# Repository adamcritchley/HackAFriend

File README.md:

# Hack-A-Friend Handheld Gaming Console

### Hone your hacking skills with the **Hack-A-Friend** gaming handheld!  
Delve into epic **CTF attack and defend** style games with your friends. Challenge opponents by **attacking their devices** while defending your own. The winner unleashes a **devastating payload** to dominate their opponent’s game.

---

## 🔥 Features

- **CTF-style gameplay** – Attack and defend devices in real-time battles.
- **Custom payloads** – Winners can craft unique in-game exploits.
- **Open-source** – Clone our upcoming [GitHub repository](#) and create your own games and payloads.
- **Interactive LEDs** – Visual cues for game status and exploit notifications.
- **Bootloader customization** – Recover or modify firmware when needed.

---

## 🔧 Hardware Specifications

- **Power System**:
  - Lithium-ion battery management chip.
  - 500mA LDO for regulated power.
  - Test points for monitoring:
    - `VCC` (battery power source).
    - `3V3` (regulated output from LDO).

- **LED Indicators**:
  - **System notifications**:
    - `PWR` (Power Health LED).
    - `CHG` (Battery Charging LED).
  - **Game Status**:
    - **NeoPixel**:
      - Off – Game idle.
      - Green – Game active.
      - Red – Device under exploitation.
    - **User-Controlled LEDs**:
      - Two standard LEDs for custom exploit visualizations.

- **Debugging & Recovery**:
  - **Test points** for SDA & SCL (I2C debugging with digital signal analyzer).
  - **Bootloader Recovery**:
    - Uses **10-pin ARM TagConnect footprint** (`TC2050-IDC-NL` cable).
    - Compatible with **SWD** and **JTAG** devices like `nRF52840 DK`.
    - Recovery via `nrf-utils` and official bootloader image.
    - **Segger J-Link compatibility

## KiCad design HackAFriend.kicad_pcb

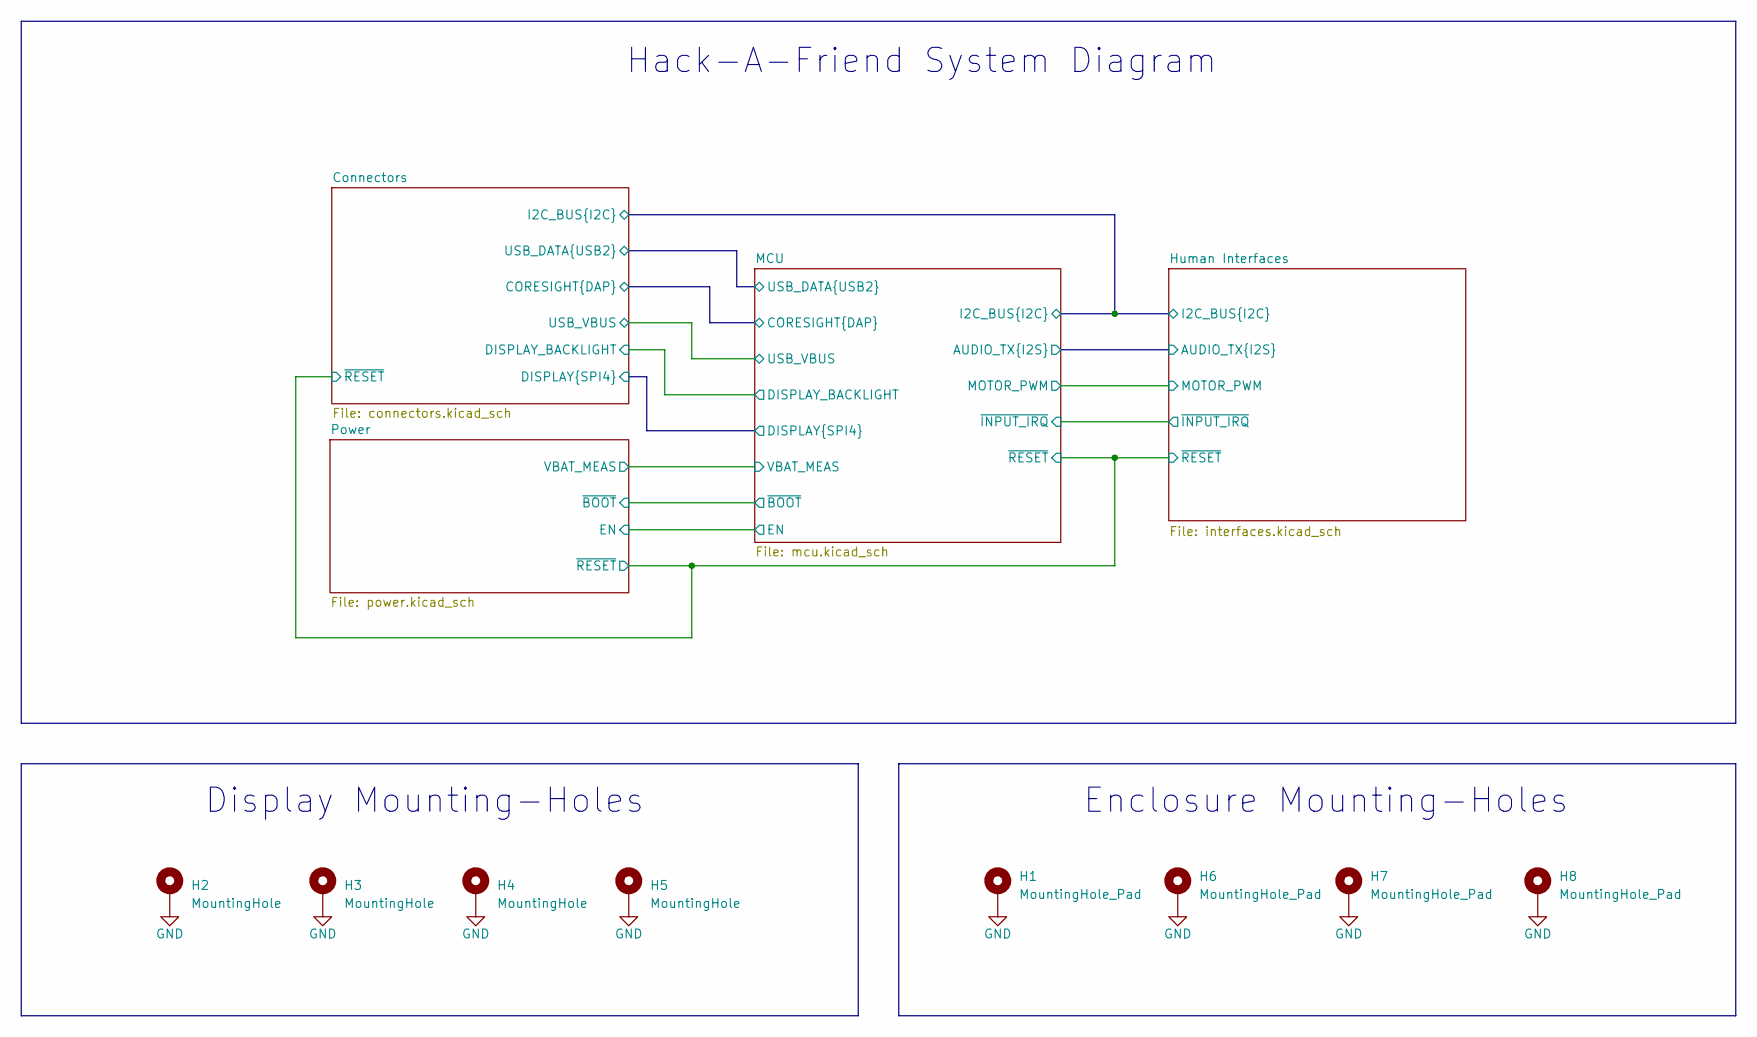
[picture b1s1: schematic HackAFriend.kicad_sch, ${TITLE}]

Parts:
H1, H6, H7, H8: MountingHole_Pad; MountingHole_2.7mm_M2.5_DIN965_Pad
H2, H3, H4, H5: MountingHole; MountingHole_2.5mm_Pad

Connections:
GND: H1.1, H2.1, H3.1, H4.1, H5.1, H6.1, H7.1, H8.1; also elsewhere on the board

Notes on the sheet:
Display Mounting-Holes
Hack-A-Friend System Diagram
Enclosure Mounting-Holes

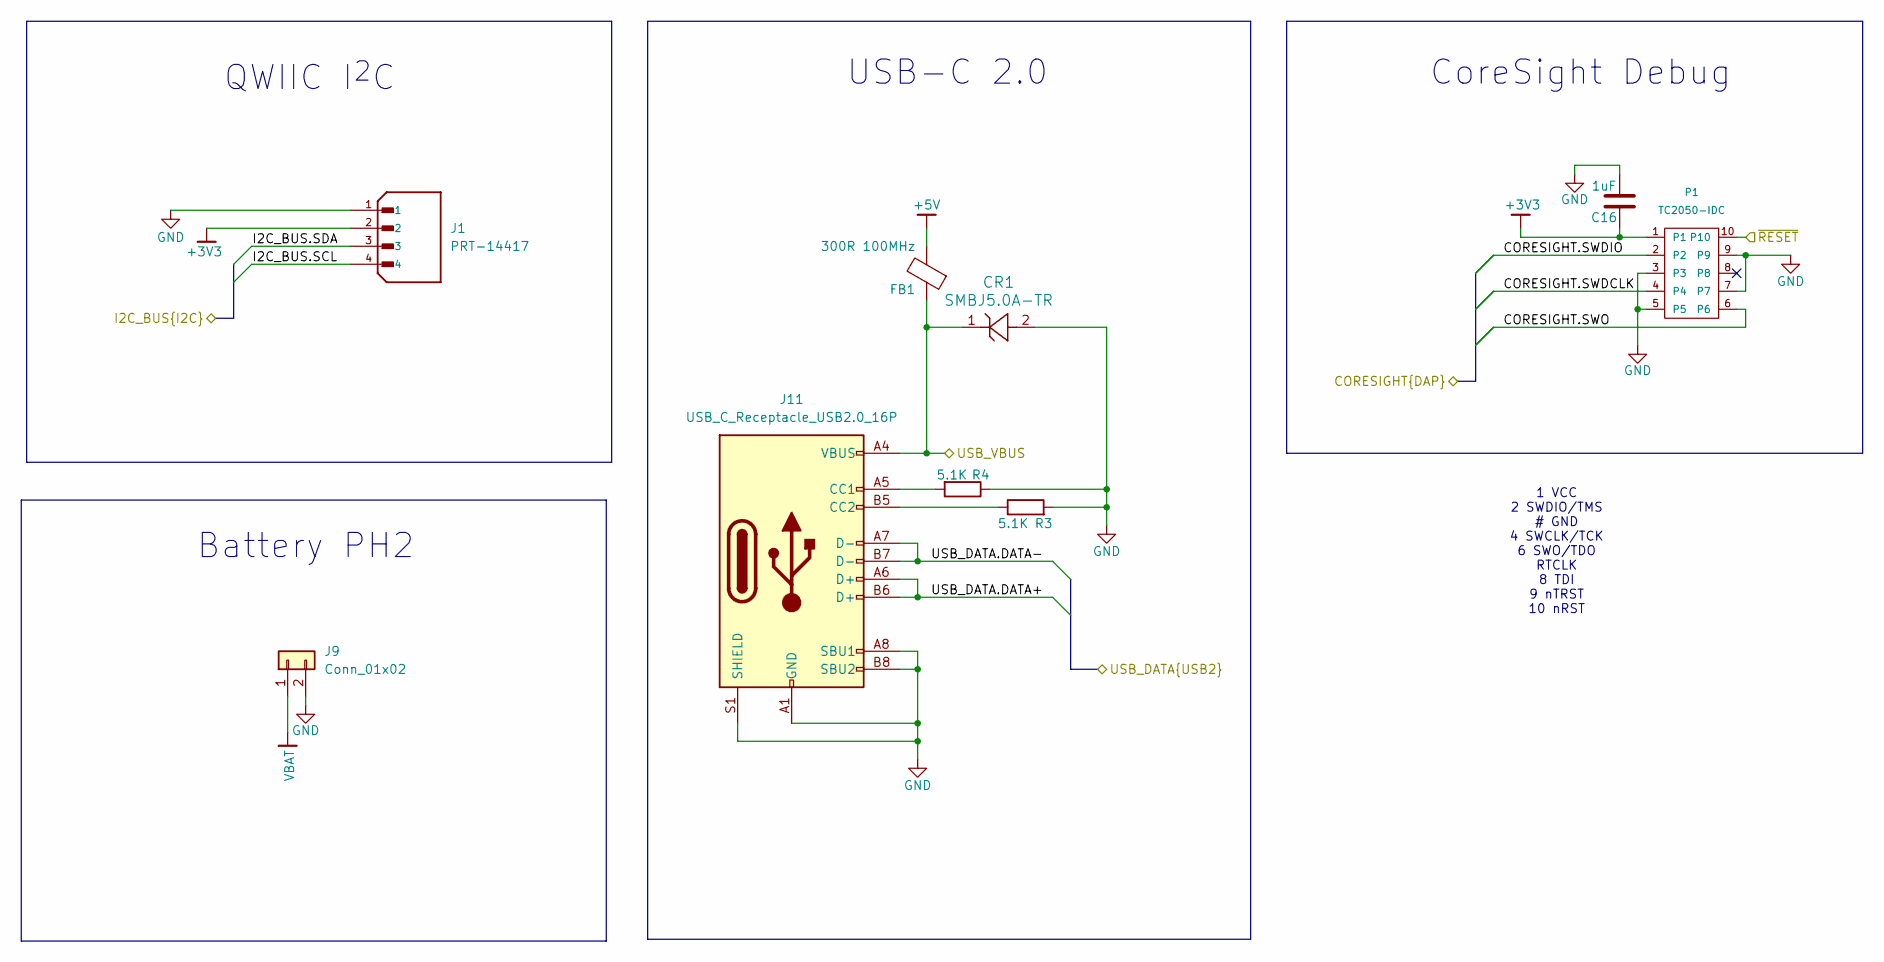
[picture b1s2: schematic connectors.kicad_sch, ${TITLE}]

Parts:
C16: 1uF; C_0402_1005Metric
CR1: SMBJ5.0A-TR; SMB_STM
FB1: 300R 100MHz; L_0805_2012Metric
J1: PRT-14417; SPARKFUN_PRT-14417; PARTREV NA
J9: Conn_01x02; JST_PH_S2B-PH-K_1x02_P2.00mm_Horizontal
J11: USB_C_Receptacle_USB2.0_16P; USB_C_Receptacle_GCT_USB4105-xx-A_16P_TopMnt_Horizontal
P1: TC2050-IDC; Tag-Connect_TC2050-IDC-FP_2x05_P1.27mm_Vertical
R3, R4: 5.1K; R_0402_1005Metric

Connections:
+3V3: C16.1, J1.2, P1.1; also elsewhere on the board
+5V: FB1.2; also elsewhere on the board
/Connectors/CORESIGHT.SWDCLK: P1.4; also elsewhere on the board
/Connectors/CORESIGHT.SWDIO: P1.2; also elsewhere on the board
/Connectors/CORESIGHT.SWO: P1.6; also elsewhere on the board
/Connectors/I2C_BUS.SCL: J1.4; also elsewhere on the board
/Connectors/I2C_BUS.SDA: J1.3; also elsewhere on the board
/Connectors/USB_DATA.DATA+: J11.A6 (D+), J11.B6 (D+); also elsewhere on the board
/Connectors/USB_DATA.DATA-: J11.A7 (D-), J11.B7 (D-); also elsewhere on the board
/Connectors/USB_VBUS: CR1.1, FB1.1, J11.A4 (VBUS), J11.A9 (VBUS), J11.B4 (VBUS), J11.B9 (VBUS); also elsewhere on the board
/Connectors/~RESET: P1.10; also elsewhere on the board
GND: C16.2, CR1.2, J1.1, J9.2, J11.A1 (GND), J11.A8 (SBU1), J11.A12 (GND), J11.B1 (GND), J11.B8 (SBU2), J11.B12 (GND), J11.S1 (SHIELD), P1.3, P1.5, P1.7, P1.9, R3.2, R4.1; also elsewhere on the board
unnamed: J11.A5 (CC1), R4.2
unnamed: J11.B5 (CC2), R3.1
VBAT: J9.1; also elsewhere on the board

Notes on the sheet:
USB-C 2.0
Battery PH2
QWIIC I^{2}C
1 VCC 2 SWDIO/TMS # GND 4 SWCLK/TCK 6 SWO/TDO RTCLK 8 TDI 9 nTRST 10 nRST
CoreSight Debug

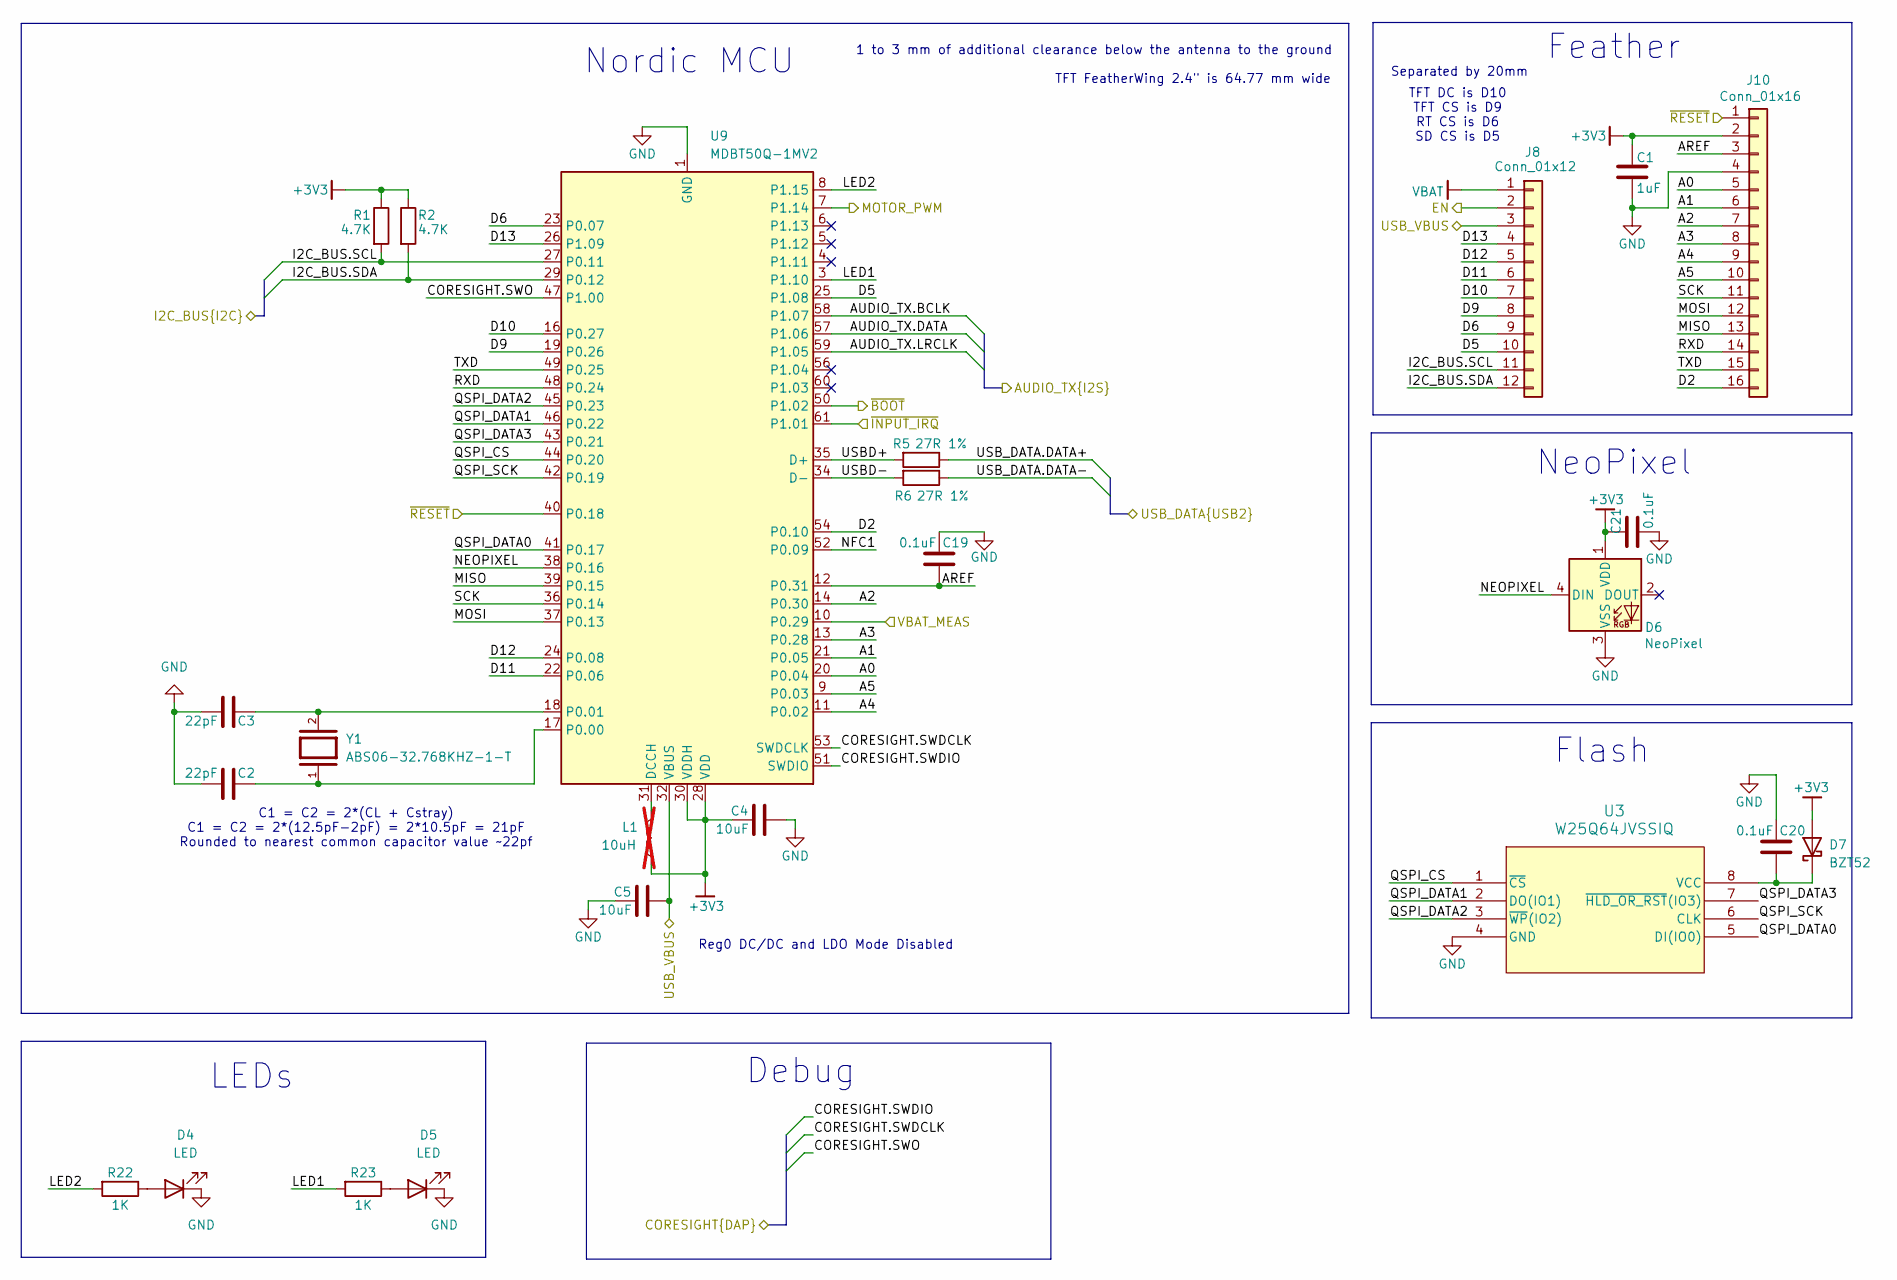
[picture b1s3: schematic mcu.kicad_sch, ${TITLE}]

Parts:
C1: 1uF; C_0402_1005Metric
C2, C3: 22pF; C_0603_1608Metric
C4, C5: 10uF; C_0603_1608Metric
C19, C20, C21: 0.1uF; C_0402_1005Metric
D4, D5: LED; LED_0603_1608Metric
D6: NeoPixel; LED_WS2812B_PLCC4_5.0x5.0mm_P3.2mm
D7: BZT52; D_0402_1005Metric
J8: Conn_01x12; PinHeader_1x12_P2.54mm_Vertical_SMD_Pin1Left
J10: Conn_01x16; PinHeader_1x16_P2.54mm_Vertical_SMD_Pin1Left
L1: 10uH; L_0603_1608Metric; not fitted
R1, R2: 4.7K; R_0603_1608Metric
R5, R6: 27R 1%; R_0402_1005Metric
R22, R23: 1K; R_0603_1608Metric
U3: W25Q64JVSSIQ; SOIC-8_5P28X5P28_WIN
U9: MDBT50Q-1MV2; Raytac_MDBT50Q
Y1: ABS06-32.768KHZ-1-T; XTAL_ABS06-32.768KHZ-1-T; PARTREV 4/25/2022

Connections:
+3V3: C1.1, C4.2, C21.2, D6.1 (VDD), D7.2 (A), J10.2, L1.1, R1.1, R2.1, U9.28 (VDD), U9.30 (VDDH); also elsewhere on the board
/Connectors/CORESIGHT.SWDCLK: U9.53 (SWDCLK); also elsewhere on the board
/Connectors/CORESIGHT.SWDIO: U9.51 (SWDIO); also elsewhere on the board
/Connectors/CORESIGHT.SWO: U9.47 (P1.00); also elsewhere on the board
/Connectors/I2C_BUS.SCL: J8.11, R1.2, U9.27 (P0.11); also elsewhere on the board
/Connectors/I2C_BUS.SDA: J8.12, R2.2, U9.29 (P0.12); also elsewhere on the board
/Connectors/USB_DATA.DATA+: R5.1; also elsewhere on the board
/Connectors/USB_DATA.DATA-: R6.1; also elsewhere on the board
/Connectors/USB_VBUS: C5.1, J8.3, U9.32 (VBUS); also elsewhere on the board
/Connectors/~RESET: J10.1, U9.40 (P0.18); also elsewhere on the board
/Human Interfaces/AUDIO_TX.BCLK: U9.58 (P1.07); also elsewhere on the board
/Human Interfaces/AUDIO_TX.DATA: U9.57 (P1.06); also elsewhere on the board
/Human Interfaces/AUDIO_TX.LRCLK: U9.59 (P1.05); also elsewhere on the board
/Human Interfaces/MOTOR_PWM: U9.7 (P1.14); also elsewhere on the board
/Human Interfaces/~INPUT_IRQ: U9.61 (P1.01); also elsewhere on the board
/MCU/A0: J10.5, U9.20 (P0.04)
/MCU/A1: J10.6, U9.21 (P0.05)
/MCU/A2: J10.7, U9.14 (P0.30)
/MCU/A3: J10.8, U9.13 (P0.28)
/MCU/A4: J10.9, U9.11 (P0.02)
/MCU/A5: J10.10, U9.9 (P0.03)
/MCU/AREF: C19.1, J10.3, U9.12 (P0.31)
/MCU/D2: J10.16, U9.54 (P0.10)
/MCU/D5: J8.10, U9.25 (P1.08)
/MCU/D6: J8.9, U9.23 (P0.07)
/MCU/D9: J8.8, U9.19 (P0.26)
/MCU/D10: J8.7, U9.16 (P0.27)
/MCU/D11: J8.6, U9.22 (P0.06)
/MCU/D12: J8.5, U9.24 (P0.08)
/MCU/D13: J8.4, U9.26 (P1.09)
/MCU/EN: J8.2; also elsewhere on the board
/MCU/LED1: R23.2, U9.3 (P1.10)
/MCU/LED2: R22.2, U9.8 (P1.15)
/MCU/MISO: J10.13, U9.39 (P0.15)
/MCU/MOSI: J10.12, U9.37 (P0.13)
/MCU/NEOPIXEL: D6.4 (DIN), U9.38 (P0.16)
/MCU/NFC1: U9.52 (P0.09)
/MCU/QSPI_CS: U3.1 (~CS), U9.44 (P0.20)
/MCU/QSPI_DATA0: U3.5 (DI(IO0)), U9.41 (P0.17)
/MCU/QSPI_DATA1: U3.2 (DO(IO1)), U9.46 (P0.22)
/MCU/QSPI_DATA2: U3.3 (~WP(IO2)), U9.45 (P0.23)
/MCU/QSPI_DATA3: U3.7 (~HLD_OR_RST(IO3)), U9.43 (P0.21)
/MCU/QSPI_SCK: U3.6 (CLK), U9.42 (P0.19)
/MCU/RXD: J10.14, U9.48 (P0.24)
/MCU/SCK: J10.11, U9.36 (P0.14)
/MCU/TXD: J10.15, U9.49 (P0.25)
/MCU/USBD+: R5.2, U9.35 (D+)
/MCU/USBD-: R6.2, U9.34 (D-)
/MCU/VBAT_MEAS: U9.10 (P0.29); also elsewhere on the board
/MCU/~BOOT: U9.50 (P1.02); also elsewhere on the board
GND: C1.2, C2.1, C3.1, C4.1, C5.2, C19.2, C20.2, C21.1, D4.1 (K), D5.1 (K), D6.3 (VSS), J10.4, U3.4 (GND), U9.1 (GND), U9.2 (GND), U9.15 (GND), U9.33 (GND), U9.55 (GND); also elsewhere on the board
unnamed: D4.2 (A), R22.1
unnamed: D5.2 (A), R23.1
unnamed: C20.1, D7.1 (K), U3.8 (VCC)
unnamed: L1.2, U9.31 (DCCH)
unnamed: C2.2, U9.17 (P0.00), Y1.1
unnamed: C3.2, U9.18 (P0.01), Y1.2
VBAT: J8.1; also elsewhere on the board

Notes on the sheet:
TFT DC is D10 TFT CS is D9 RT CS is D6 SD CS is D5
Debug
C1 = C2 = 2*(CL + Cstray) C1 = C2 = 2*(12.5pF-2pF) = 2*10.5pF = 21pF Rounded to nearest common capacitor value ~22pf
LEDs
Feather
Reg0 DC/DC and LDO Mode Disabled
NeoPixel
TFT FeatherWing 2.4" is 64.77 mm wide
Separated by 20mm
Flash
1 to 3 mm of additional clearance below the antenna to the ground
Nordic MCU

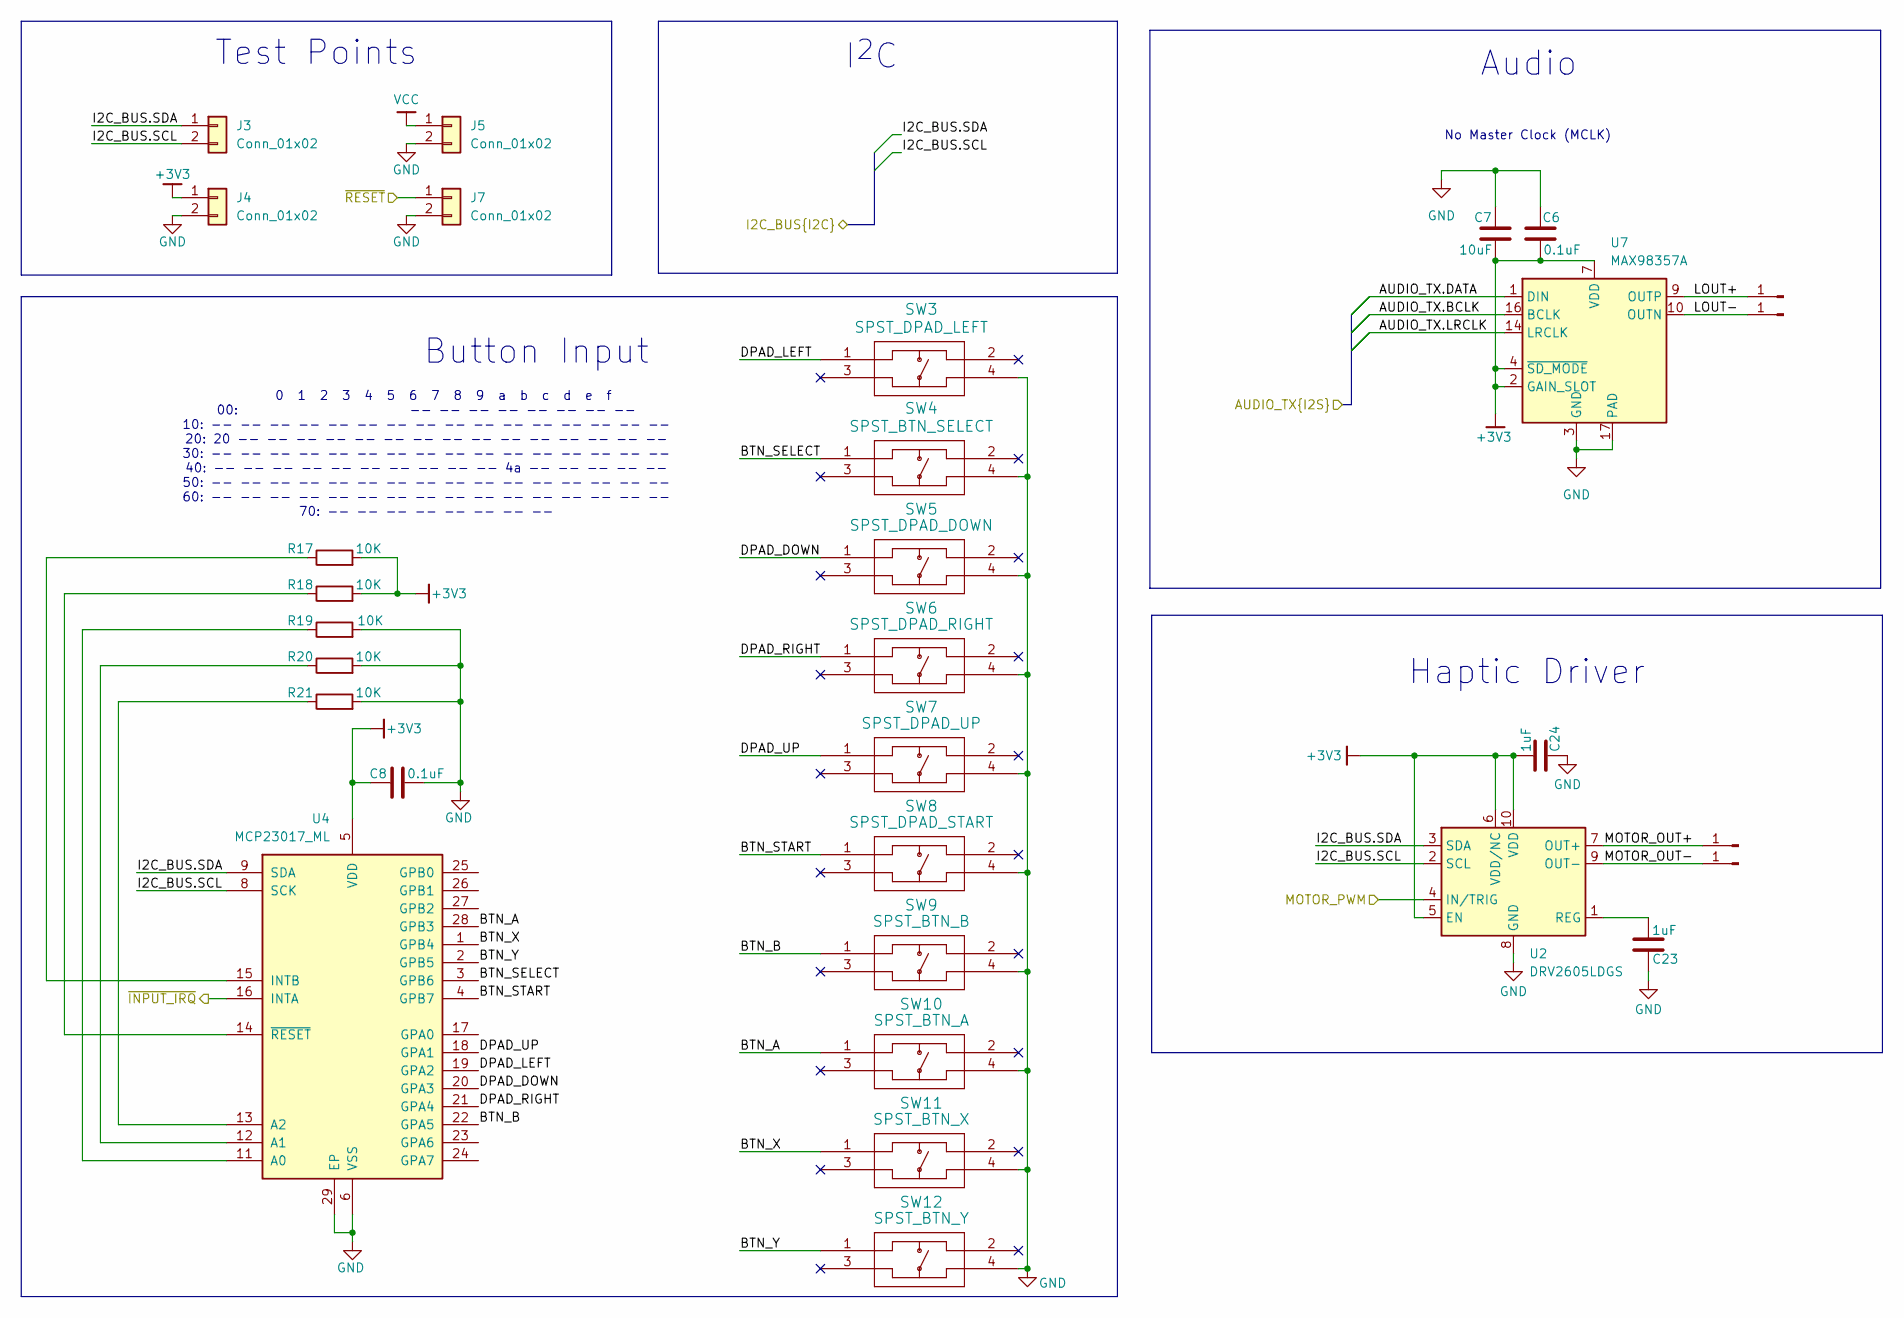
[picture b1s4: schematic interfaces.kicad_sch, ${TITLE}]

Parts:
C6, C8: 0.1uF; C_0402_1005Metric
C7: 10uF; C_0603_1608Metric
C23, C24: 1uF; C_0603_1608Metric
J3, J4, J5, J7: Conn_01x02; PinHeader_1x02_P2.54mm_Vertical
LPAD_OUT+1, LPAD_OUT+2: Conn_01x01_Pin; SolderWirePad_1x01_SMD_1x2mm
LPAD_OUT-1, LPAD_OUT-2: Conn_01x01_Pin; SolderWirePad_1x01_SMD_1x2mm
R17, R18, R19, R20, R21: 10K; C_0402_1005Metric
SW3: SPST_DPAD_LEFT; SW_PTS_647_SN50_SMTR2_LFS; PARTREV 4 Apr 22; DigiKey_Part_Number PTS647SN50SMTR2LFSTR-ND
SW4: SPST_BTN_SELECT; SW_PTS_647_SN50_SMTR2_LFS; PARTREV 4 Apr 22; DigiKey_Part_Number PTS647SN50SMTR2LFSTR-ND
SW5: SPST_DPAD_DOWN; SW_PTS_647_SN50_SMTR2_LFS; PARTREV 4 Apr 22; DigiKey_Part_Number PTS647SN50SMTR2LFSTR-ND
SW6: SPST_DPAD_RIGHT; SW_PTS_647_SN50_SMTR2_LFS; PARTREV 4 Apr 22; DigiKey_Part_Number PTS647SN50SMTR2LFSTR-ND
SW7: SPST_DPAD_UP; SW_PTS_647_SN50_SMTR2_LFS; PARTREV 4 Apr 22; DigiKey_Part_Number PTS647SN50SMTR2LFSTR-ND
SW8: SPST_DPAD_START; SW_PTS_647_SN50_SMTR2_LFS; PARTREV 4 Apr 22; DigiKey_Part_Number PTS647SN50SMTR2LFSTR-ND
SW9: SPST_BTN_B; SW_PTS_647_SN50_SMTR2_LFS; PARTREV 4 Apr 22; DigiKey_Part_Number PTS647SN50SMTR2LFSTR-ND
SW10: SPST_BTN_A; SW_PTS_647_SN50_SMTR2_LFS; PARTREV 4 Apr 22; DigiKey_Part_Number PTS647SN50SMTR2LFSTR-ND
SW11: SPST_BTN_X; SW_PTS_647_SN50_SMTR2_LFS; PARTREV 4 Apr 22; DigiKey_Part_Number PTS647SN50SMTR2LFSTR-ND
SW12: SPST_BTN_Y; SW_PTS_647_SN50_SMTR2_LFS; PARTREV 4 Apr 22; DigiKey_Part_Number PTS647SN50SMTR2LFSTR-ND
U2: DRV2605LDGS; VSSOP-10_3x3mm_P0.5mm
U4: MCP23017_ML; QFN-28-1EP_6x6mm_P0.65mm_EP4.25x4.25mm
U7: MAX98357A; TQFN-16-1EP_3x3mm_P0.5mm_EP1.23x1.23mm

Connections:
+3V3: C6.1, C7.1, C8.2, C24.2, J4.1, R17.2, R18.2, U2.5 (EN), U2.6 (VDD/NC), U2.10 (VDD), U4.5 (VDD), U7.2 (GAIN_SLOT), U7.4 (~SD_MODE), U7.7 (VDD), U7.8 (VDD); also elsewhere on the board
/Connectors/I2C_BUS.SCL: J3.2, U2.2 (SCL), U4.8 (SCK); also elsewhere on the board
/Connectors/I2C_BUS.SDA: J3.1, U2.3 (SDA), U4.9 (SDA); also elsewhere on the board
/Connectors/~RESET: J7.1; also elsewhere on the board
/Human Interfaces/AUDIO_TX.BCLK: U7.16 (BCLK); also elsewhere on the board
/Human Interfaces/AUDIO_TX.DATA: U7.1 (DIN); also elsewhere on the board
/Human Interfaces/AUDIO_TX.LRCLK: U7.14 (LRCLK); also elsewhere on the board
/Human Interfaces/BTN_A: SW10.1, U4.28 (GPB3)
/Human Interfaces/BTN_B: SW9.1, U4.22 (GPA5)
/Human Interfaces/BTN_SELECT: SW4.1, U4.3 (GPB6)
/Human Interfaces/BTN_START: SW8.1, U4.4 (GPB7)
/Human Interfaces/BTN_X: SW11.1, U4.1 (GPB4)
/Human Interfaces/BTN_Y: SW12.1, U4.2 (GPB5)
/Human Interfaces/DPAD_DOWN: SW5.1, U4.20 (GPA3)
/Human Interfaces/DPAD_LEFT: SW3.1, U4.19 (GPA2)
/Human Interfaces/DPAD_RIGHT: SW6.1, U4.21 (GPA4)
/Human Interfaces/DPAD_UP: SW7.1, U4.18 (GPA1)
/Human Interfaces/LOUT+: LPAD_OUT+2.1, U7.9 (OUTP)
/Human Interfaces/LOUT-: LPAD_OUT-2.1, U7.10 (OUTN)
/Human Interfaces/MOTOR_OUT+: LPAD_OUT+1.1, U2.7 (OUT+)
/Human Interfaces/MOTOR_OUT-: LPAD_OUT-1.1, U2.9 (OUT-)
/Human Interfaces/MOTOR_PWM: U2.4 (IN/TRIG); also elsewhere on the board
/Human Interfaces/~INPUT_IRQ: U4.16 (INTA); also elsewhere on the board
GND: C6.2, C7.2, C8.1, C23.1, C24.1, J4.2, J5.2, J7.2, R19.2, R20.2, R21.2, SW3.4, SW4.4, SW5.4, SW6.4, SW7.4, SW8.4, SW9.4, SW10.4, SW11.4, SW12.4, U2.8 (GND), U4.6 (VSS), U4.29 (EP), U7.3 (GND), U7.11 (GND), U7.15 (GND), U7.17 (PAD); also elsewhere on the board
unnamed: C23.2, U2.1 (REG)
unnamed: R19.1, U4.11 (A0)
unnamed: R20.1, U4.12 (A1)
unnamed: R21.1, U4.13 (A2)
unnamed: R17.1, U4.15 (INTB)
unnamed: R18.1, U4.14 (~RESET)
VCC: J5.1; also elsewhere on the board

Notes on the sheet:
Test Points
Audio
I^{2}C
No Master Clock (MCLK)
Button Input
0 1 2 3 4 5 6 7 8 9 a b c d e f 00: -- -- -- -- -- -- -- -- 10: -- -- -- -- -- -- -- -- -- -- -- -- -- -- -- -- 20: 20 -- -- -- -- -- -- -- -- -- -- -- -- -- -- -- 30: -- -- -- -- -- -- -- -- -- -- -- -- -- -- -- -- 40: -- -- -- -- -- -- -- -- -- -- 4a -- -- -- -- -- 50: -- -- -- -- -- -- -- -- -- 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
Haptic Driver

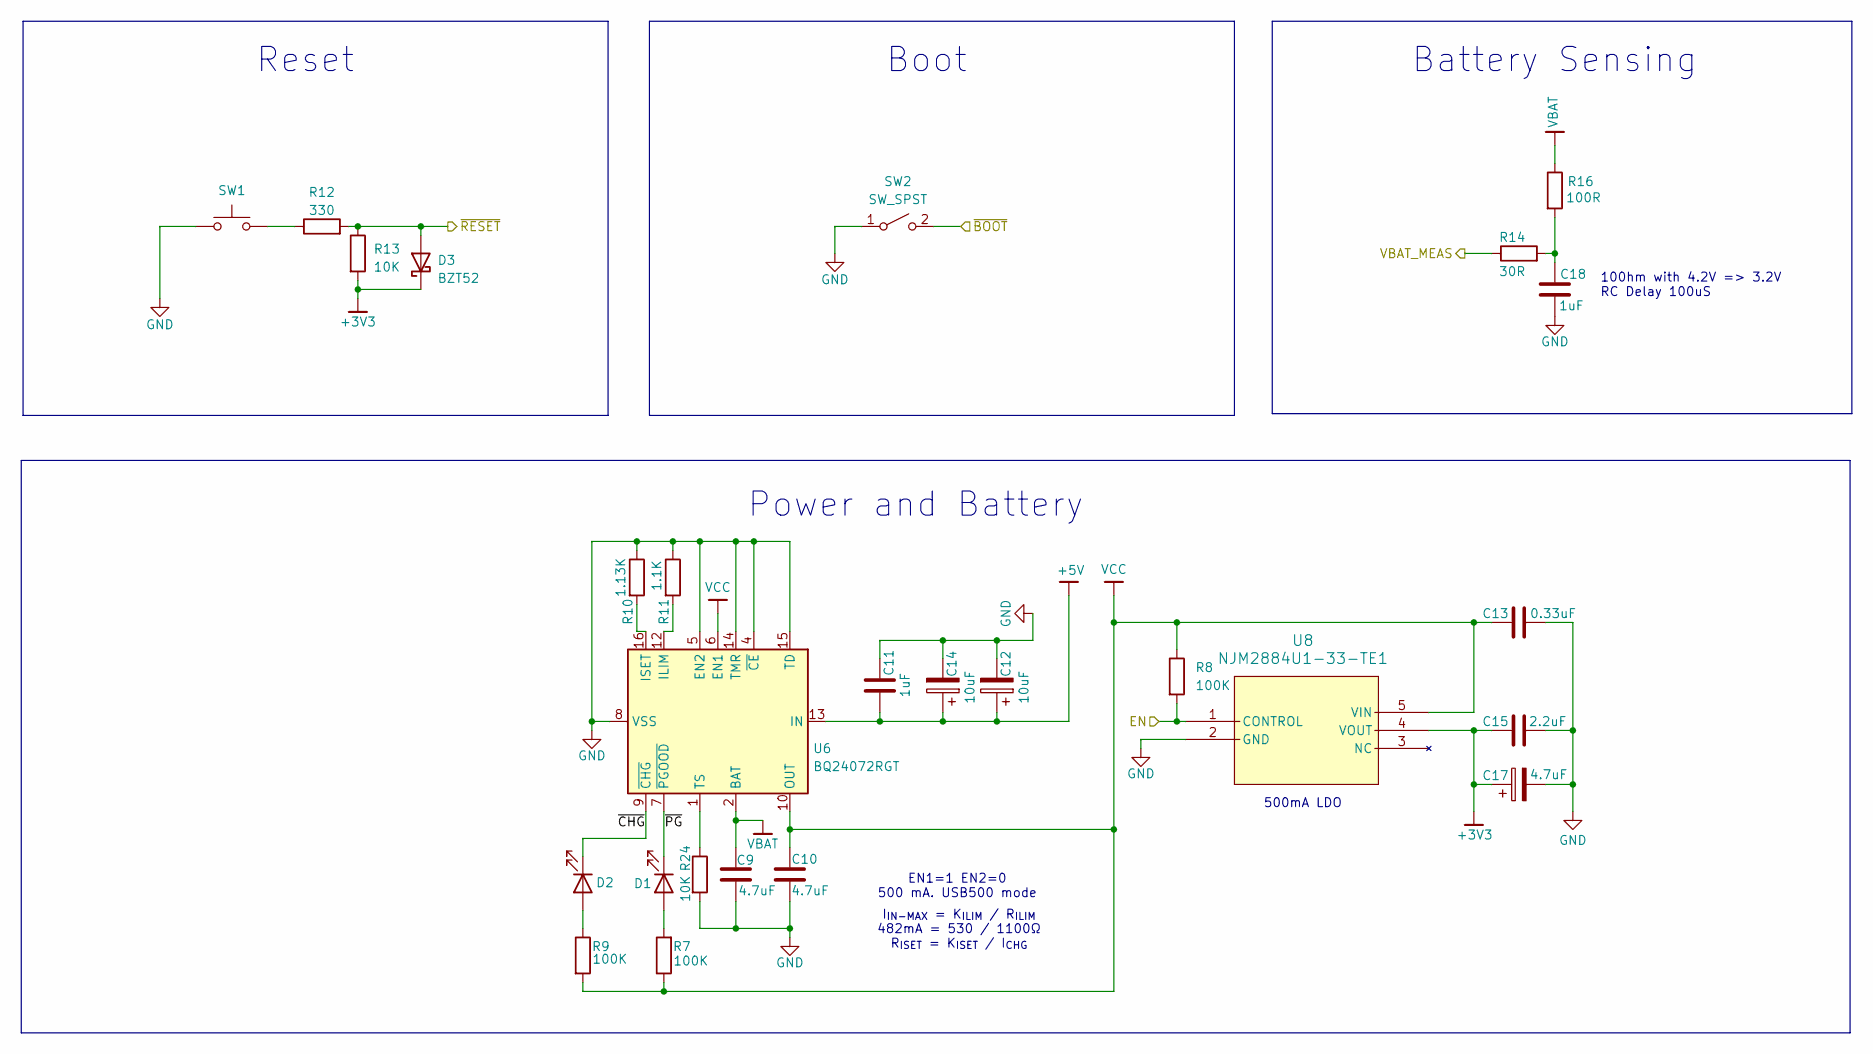
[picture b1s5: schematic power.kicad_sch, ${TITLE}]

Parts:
C9, C10: 4.7uF; C_0603_1608Metric
C11: 1uF; C_0603_1608Metric
C12, C14: 10uF; CP_EIA-3528-15_AVX-H
C13: 0.33uF; C_0603_1608Metric
C15: 2.2uF; C_0603_1608Metric
C17: 4.7uF; CP_EIA-1608-08_AVX-J
C18: 1uF; C_0402_1005Metric
D1, D2: LTST-S270TBKT; LED_0603_1608Metric
D3: BZT52; D_0402_1005Metric
R7, R8, R9: 100K; R_0603_1608Metric
R10: 1.13K; R_0402_1005Metric
R11: 1.1K; R_0402_1005Metric
R12: 330; R_0603_1608Metric
R13, R24: 10K; R_0402_1005Metric
R14: 30R; R_0402_1005Metric
R16: 100R; R_0402_1005Metric
SW1: SW_SPST_Omron_B3F-315x_Angled
SW2: SW_SPST; SW_SPST_B3U-1000P
U6: BQ24072RGT; VQFN-16-1EP_3x3mm_P0.5mm_EP1.6x1.6mm
U8: NJM2884U1-33-TE1; SOT89-5-1&slash_2_NWJ

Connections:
+3V3: C15.1, C17.1, D3.1 (K), R13.2, U8.4 (VOUT); also elsewhere on the board
+5V: C11.2, C12.1, C14.1, U6.13 (IN); also elsewhere on the board
/Connectors/~RESET: D3.2 (A), R12.2, R13.1; also elsewhere on the board
/MCU/EN: R8.2, U8.1 (CONTROL); also elsewhere on the board
/MCU/VBAT_MEAS: R14.1; also elsewhere on the board
/MCU/~BOOT: SW2.2 (B); also elsewhere on the board
/Power/~CHG: D2.1 (K), U6.9 (~CHG)
/Power/~PG: D1.1 (K), U6.7 (~PGOOD)
GND: C9.2, C10.2, C11.1, C12.2, C13.2, C14.2, C15.2, C17.2, C18.2, R10.1, R11.1, R24.2, SW1.1, SW2.1 (A), U6.4 (~CE), U6.5 (EN2), U6.8 (VSS), U6.14 (TMR), U6.15 (TD), U6.17 (VSS), U8.2 (GND); also elsewhere on the board
unnamed: C18.1, R14.2, R16.2
unnamed: D1.2 (A), R7.2
unnamed: D2.2 (A), R9.1
unnamed: R12.1, SW1.2
unnamed: R11.2, U6.12 (ILIM)
unnamed: R10.2, U6.16 (ISET)
unnamed: R24.1, U6.1 (TS)
VBAT: C9.1, R16.1, U6.2 (BAT), U6.3 (BAT); also elsewhere on the board
VCC: C10.1, C13.1, R7.1, R8.1, R9.2, U6.6 (EN1), U6.10 (OUT), U6.11 (OUT), U8.5 (VIN); also elsewhere on the board

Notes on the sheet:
Power and Battery
500mA LDO
I_{IN-MAX} = K_{ILIM} / R_{ILIM} 482mA = 530 / 1100Ω R_{ISET} = K_{ISET} / I_{CHG}
100hm with 4.2V => 3.2V RC Delay 100uS
Reset
Boot
EN1=1 EN2=0 500 mA. USB500 mode
Battery Sensing

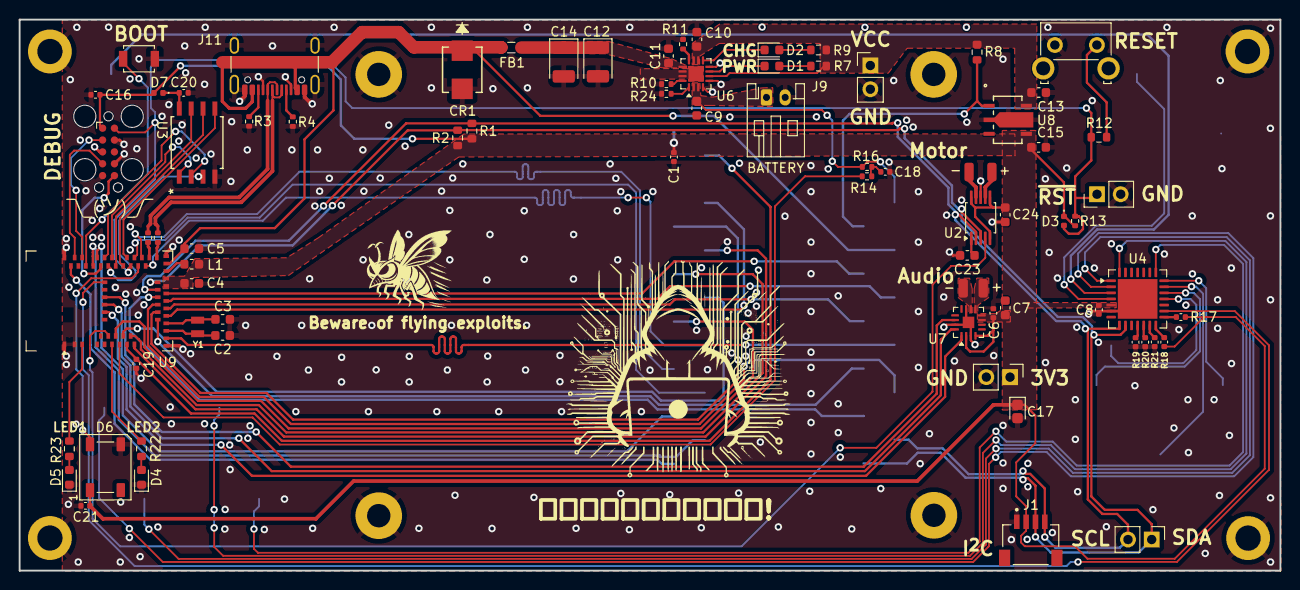
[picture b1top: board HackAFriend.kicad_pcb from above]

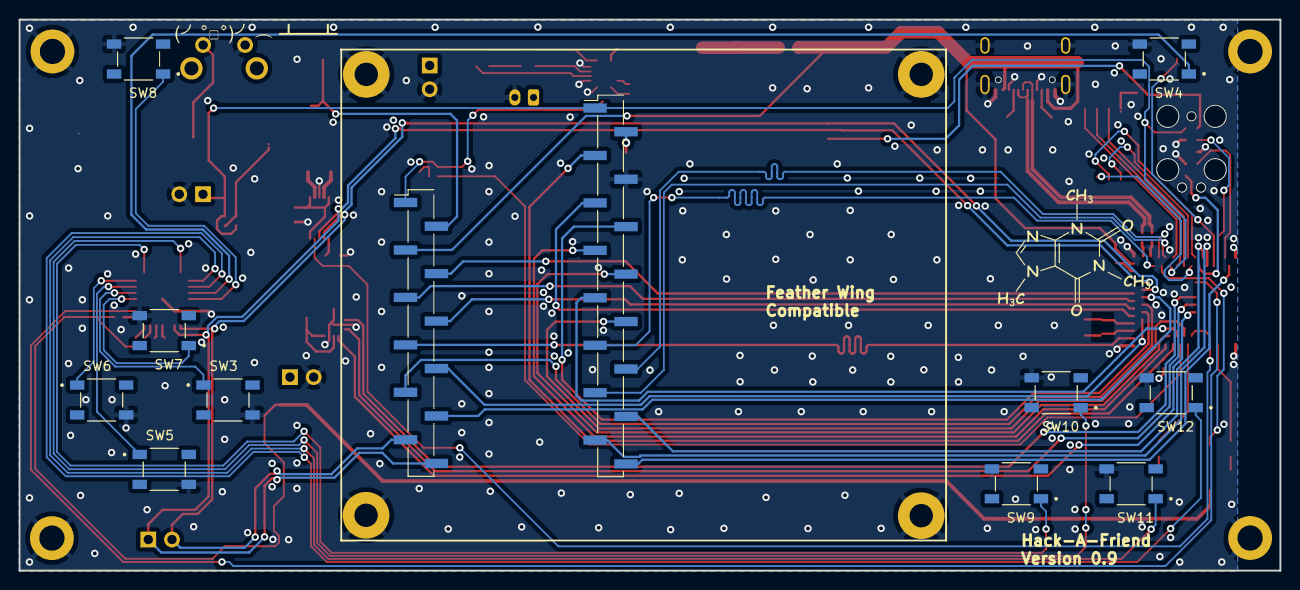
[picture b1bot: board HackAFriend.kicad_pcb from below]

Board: 2 copper layers, 135.0 x 59.0 mm, 98 parts (12 on the bottom side), 90 nets.

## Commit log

2025-05-06 Initial release
    HackAFriend v1A release
2025-05-06 Create Hackafriend_BOM_PCBWay.xlsx
    Add PCBWay BOM
2025-06-01 Release candidate
    Changed USBC connector, changed TagConnect to use footprint with legs, move NRF52 to edge of board, clean up traces
2025-06-03 Change button footprint
    Change button footprint to PTS647 and add a few more stitching vias.
2025-06-06 Update part numbers
    Update part numbers for 12 and 16 PIN SMD 2.54mm pins and USB-C 2.0 connector.
2025-06-21 Add bypass capacitor
    Added bypass capacitor on VBUS for MCU
2025-08-06 Tweak locations and add a bypass capacitor for VBUS
2025-08-06 Clean up locations
2025-08-10 Replaced DA7280 with DRV2605
    Replaced DA7280 with DRV2605 to simplify board support code in Hack-A-Friend Arduino Library.
2025-11-09 Changed reset button, upgrade to new KiCad
2025-11-30 Added MP part number fields to schematic and PCB design,

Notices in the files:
parts and their libraries:
LICENSE: CC-BY-SA-4.0
